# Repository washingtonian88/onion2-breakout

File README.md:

# onion2-breakout
Breakout board for the onion omega 2 with 5V power provided by a micro-USB connector and an interface for connecting a USB device to the Omega2.

---
This is my first attempt at designing a PCB. I decided to use KiCAD due to mild-familiarity with it and its open nature. The components were chosen to be cheap and easy to obtain (via ebay). Total cost per board is < $10 fully assembled, can be made cheaper by not populating some of the parts (USB connectors and pin headers).

---
### ToDo (before ordering):
* ~~Validate foot print for USB interfaces~~
* ~~Make sure the 2.54mm pins are spaced so they will fit on a 'normal' pcb~~
* ~~Consult some guru's on layout / design~~

---
### Rev 1 ORDERED!
Bought all of the components on eBay minus the 2.54mm 1x16 pin headers for ~$40 USD to build 10 boards. Here's to hoping for a strong tail wind for the boat. For the first round (Rev. 1) I ordered 3 boards from OSHPark.com (https://oshpark.com/shared_projects/boUh3Ezt) for $16 shipped.

---
### Rev 2
Found an issue with the USB connector schematic (pins 4 and 5 were switched). I have corrected this on the schematic and board layout. I also found the clearance to be too tight for the USB-A connector and the onion board. I moved the connector down a bit to allow for more clearance. I confirmed the seral communication via the CH340G chip and confirmed the USB host abilities via the USB A connector. Rev. 2 has been uploaded to OSHPark.com (https://oshpark.com/shared_projects/nRecWv9b).

### ToDo
* ~~Modify footprint of micro USB connector to allow larger mounting feet to properly mount.~~
* ~~Verify USB host functionality.~~ Works!
```
                      * ... ?
                      * Profit!
                __
             .-'  |
            /   <\|
           /     \'
           |_.- o-o
           / C  -._)\
          /',        |
         |   `-,_,__,'
         (,,)====[_]=|
           '.   ____/
            | -|-|_
            |____)_)    
```

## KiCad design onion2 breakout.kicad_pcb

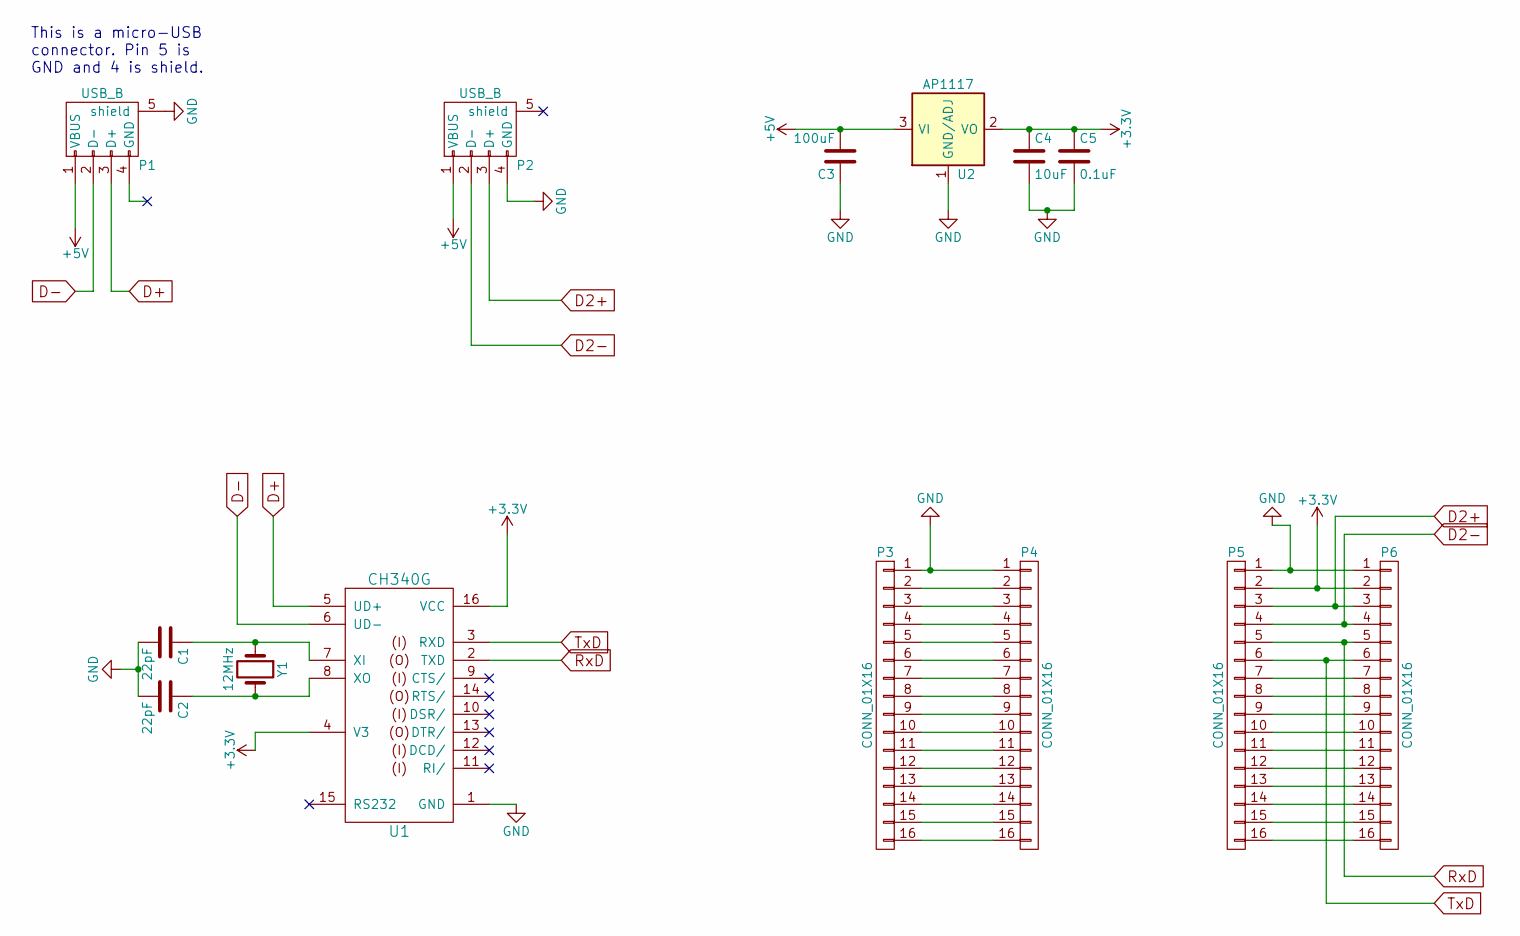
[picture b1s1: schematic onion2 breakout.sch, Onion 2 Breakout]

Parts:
C1, C2: 22pF; C_1206_HandSoldering
C3: 100uF; C_1206_HandSoldering
C4: 10uF; C_1206_HandSoldering
C5: 0.1uF; C_1206_HandSoldering
P1: USB_B; USB_B_MUSB_Straight
P2: USB_B; USB_A
P3, P6: CONN_01X16; Pin_Header_Straight_1x16_Pitch2.54mm
P4, P5: CONN_01X16; Pin_Header_Straight_1x16_Pitch2.00mm
U1: CH340G; SO-16-N
U2: AP1117; SOT-223
Y1: 12MHz; Crystal_SMD_HC49-SD_HandSoldering

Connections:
+3V3: C4.1, C5.1, P5.2, P6.2, U1.4 (V3), U1.16 (VCC), U2.2 (VO), U2.4 (VO)
+5V: C3.2, P1.1 (VBUS), P2.1 (VBUS), U2.3 (VI)
D2+: P2.3 (D+), P5.3, P6.3
D2-: P2.2 (D-), P5.4, P6.4
D+: P1.3 (D+), U1.5 (UD+)
D-: P1.2 (D-), U1.6 (UD-)
GND: C1.2, C2.2, C3.1, C4.2, C5.2, P1.5 (shield), P2.4 (GND), P3.1, P4.1, P5.1, P6.1, U1.1 (GND), U2.1 (GND/ADJ)
unnamed: C1.1, U1.7 (XI), Y1.1
unnamed: C2.1, U1.8 (XO), Y1.2
unnamed: P3.2, P4.2
unnamed: P3.3, P4.3
unnamed: P3.4, P4.4
unnamed: P3.5, P4.5
unnamed: P3.6, P4.6
unnamed: P3.7, P4.7
unnamed: P3.8, P4.8
unnamed: P3.9, P4.9
unnamed: P3.10, P4.10
unnamed: P3.11, P4.11
unnamed: P3.12, P4.12
unnamed: P3.13, P4.13
unnamed: P3.14, P4.14
unnamed: P3.15, P4.15
unnamed: P3.16, P4.16
unnamed: P5.7, P6.7
unnamed: P5.8, P6.8
unnamed: P5.9, P6.9
unnamed: P5.10, P6.10
unnamed: P5.11, P6.11
unnamed: P5.12, P6.12
unnamed: P5.13, P6.13
unnamed: P5.14, P6.14
unnamed: P5.15, P6.15
unnamed: P5.16, P6.16
RxD: P5.5, P6.5, U1.2 (TXD)
TxD: P5.6, P6.6, U1.3 (RXD)

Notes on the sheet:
This is a micro-USB connector. Pin 5 is GND and 4 is shield.

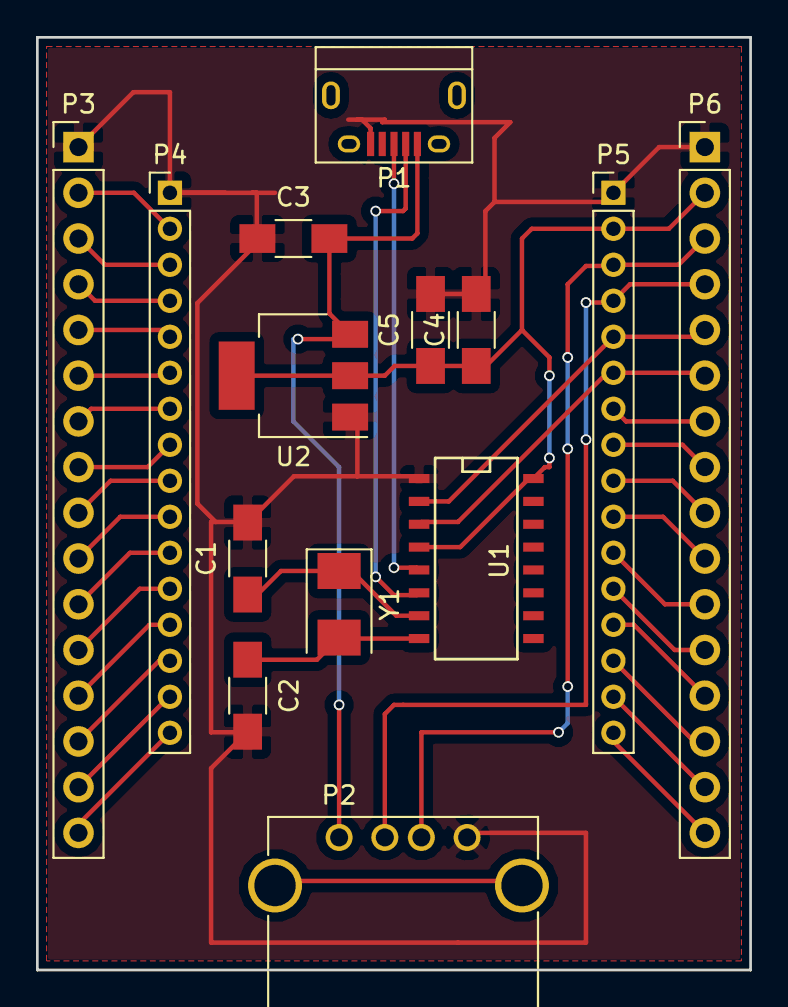
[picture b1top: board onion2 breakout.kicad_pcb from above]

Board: 2 copper layers, 39.6 x 51.8 mm, 14 parts (0 on the bottom side), 36 nets.

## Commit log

2017-03-12 Fxed Rx/Tx lines from CH340G to Onion. Adjusted header spacing to accomidate onion. Changed power/data connector from USB B to USB micro. Added BOM.
2017-04-08 Corrected issue with u-USB pinout. Moved USB A connector down a bit for more clearance. Rev 2.0
2017-04-09 Updated footprint of microUSB connector to avoid slitted hole.
2017-04-09 adding photos for hosting on github
2017-04-21 moved BOM from xlxs to csv
